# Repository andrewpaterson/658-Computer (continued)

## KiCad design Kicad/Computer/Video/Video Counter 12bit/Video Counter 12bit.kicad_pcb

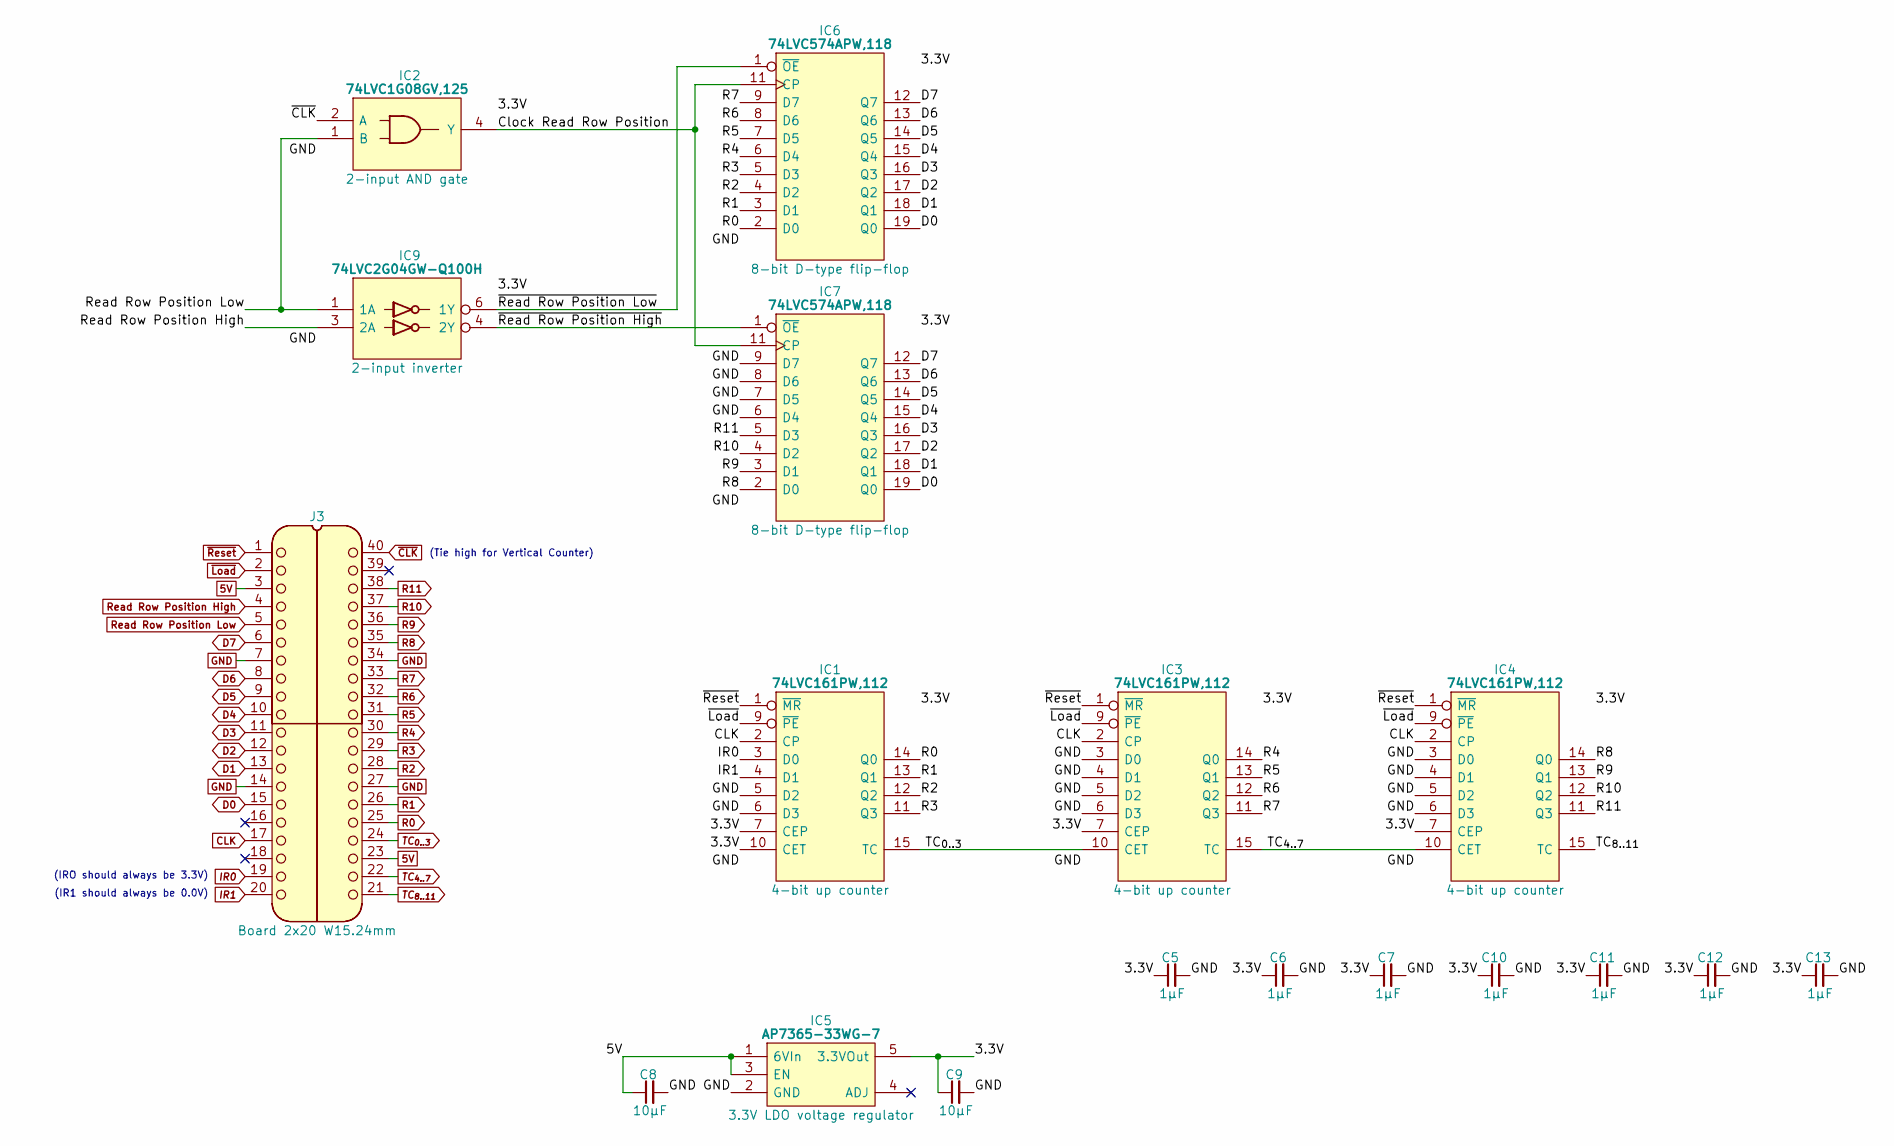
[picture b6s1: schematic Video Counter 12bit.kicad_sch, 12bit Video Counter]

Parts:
C5, C6, C7, C10, C11, C12, C13: 1μF; C_0805
C8, C9: 10µF; C_0805
IC1, IC3, IC4: 74LVC161PW,112; SOP65P640X110-16N; Mouser Part Number 771-LVC161PW112
IC2: 74LVC1G08GV,125; SOT95P275X110-5N; Manufacturer_Part_Number 74LVC1G08GV,125; Mouser Part Number 771-74LVC1G08GV
IC5: AP7365-33WG-7; SOT95P285X130-5N; Manufacturer_Part_Number AP7365-33WG-7; Mouser Part Number 621-AP7365-33WG-7
IC6, IC7: 74LVC574APW,118; SOP65P640X110-20N; Manufacturer_Part_Number 74LVC574APW,118; Mouser Part Number 771-74LVC574APW-T
IC9: 74LVC2G04GW-Q100H; SOP65P210X110-6N; Manufacturer_Part_Number 74LVC2G04GW-Q100H; Mouser Part Number 771-74LVC2G04GWQ100H
J3: Board 2x20 W15.24mm; DIP-40_Board_W15.24mm

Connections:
5V: C8.1, IC5.1 (6VIn), IC5.3 (EN), J3.3, J3.23
/3.3V: C5.1, C6.1, C7.1, C9.1, C10.1, C11.1, C12.1, C13.1, IC1.7 (CEP), IC1.10 (CET), IC1.16 (3V), IC2.5 (3V), IC3.7 (CEP), IC3.16 (3V), IC4.7 (CEP), IC4.16 (3V), IC5.5 (3.3VOut), IC6.20 (3V), IC7.20 (3V), IC9.5 (3V)
/Clock Read Row Position: IC2.4 (Y), IC6.11 (CP), IC7.11 (CP)
/~Read Row Position High: IC7.1 (~OE), IC9.4 (2Y)
/~Read Row Position Low: IC6.1 (~OE), IC9.6 (1Y)
CLK: IC1.2 (CP), IC3.2 (CP), IC4.2 (CP), J3.17
D0: IC6.19 (Q0), IC7.19 (Q0), J3.15
D1: IC6.18 (Q1), IC7.18 (Q1), J3.13
D2: IC6.17 (Q2), IC7.17 (Q2), J3.12
D3: IC6.16 (Q3), IC7.16 (Q3), J3.11
D4: IC6.15 (Q4), IC7.15 (Q4), J3.10
D5: IC6.14 (Q5), IC7.14 (Q5), J3.9
D6: IC6.13 (Q6), IC7.13 (Q6), J3.8
D7: IC6.12 (Q7), IC7.12 (Q7), J3.6
GND: C5.2, C6.2, C7.2, C8.2, C9.2, C10.2, C11.2, C12.2, C13.2, IC1.5 (D2), IC1.6 (D3), IC1.8 (GND), IC2.3 (GND), IC3.3 (D0), IC3.4 (D1), IC3.5 (D2), IC3.6 (D3), IC3.8 (GND), IC4.3 (D0), IC4.4 (D1), IC4.5 (D2), IC4.6 (D3), IC4.8 (GND), IC5.2 (GND), IC6.10 (GND), IC7.6 (D4), IC7.7 (D5), IC7.8 (D6), IC7.9 (D7), IC7.10 (GND), IC9.2 (GND), J3.7, J3.14, J3.27, J3.34
IR0: IC1.3 (D0), J3.19
IR1: IC1.4 (D1), J3.20
R0: IC1.14 (Q0), IC6.2 (D0), J3.25
R1: IC1.13 (Q1), IC6.3 (D1), J3.26
R2: IC1.12 (Q2), IC6.4 (D2), J3.28
R3: IC1.11 (Q3), IC6.5 (D3), J3.29
R4: IC3.14 (Q0), IC6.6 (D4), J3.30
R5: IC3.13 (Q1), IC6.7 (D5), J3.31
R6: IC3.12 (Q2), IC6.8 (D6), J3.32
R7: IC3.11 (Q3), IC6.9 (D7), J3.33
R8: IC4.14 (Q0), IC7.2 (D0), J3.35
R9: IC4.13 (Q1), IC7.3 (D1), J3.36
R10: IC4.12 (Q2), IC7.4 (D2), J3.37
R11: IC4.11 (Q3), IC7.5 (D3), J3.38
Read Row Position High: IC9.3 (2A), J3.4
Read Row Position Low: IC2.1 (B), IC9.1 (1A), J3.5
TC_{0..3}: IC1.15 (TC), IC3.10 (CET), J3.24
TC_{4..7}: IC3.15 (TC), IC4.10 (CET), J3.22
TC_{8..11}: IC4.15 (TC), J3.21
~CLK: IC2.2 (A), J3.40
~Load: IC1.9 (~PE), IC3.9 (~PE), IC4.9 (~PE), J3.2
~Reset: IC1.1 (~MR), IC3.1 (~MR), IC4.1 (~MR), J3.1

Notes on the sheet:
(Tie high for Vertical Counter)
(IRO should always be 3.3V)
(IR1 should always be 0.0V)

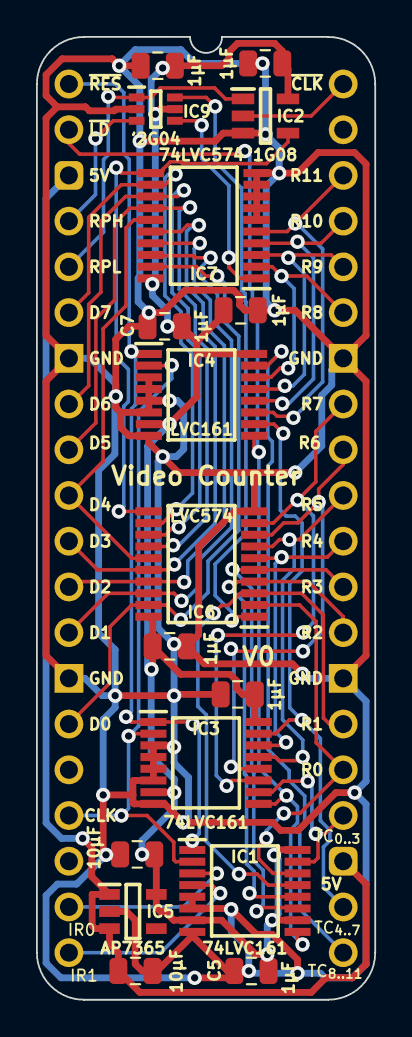
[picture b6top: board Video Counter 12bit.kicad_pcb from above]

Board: 2 copper layers, 18.8 x 53.5 mm, 18 parts (0 on the bottom side), 37 nets.

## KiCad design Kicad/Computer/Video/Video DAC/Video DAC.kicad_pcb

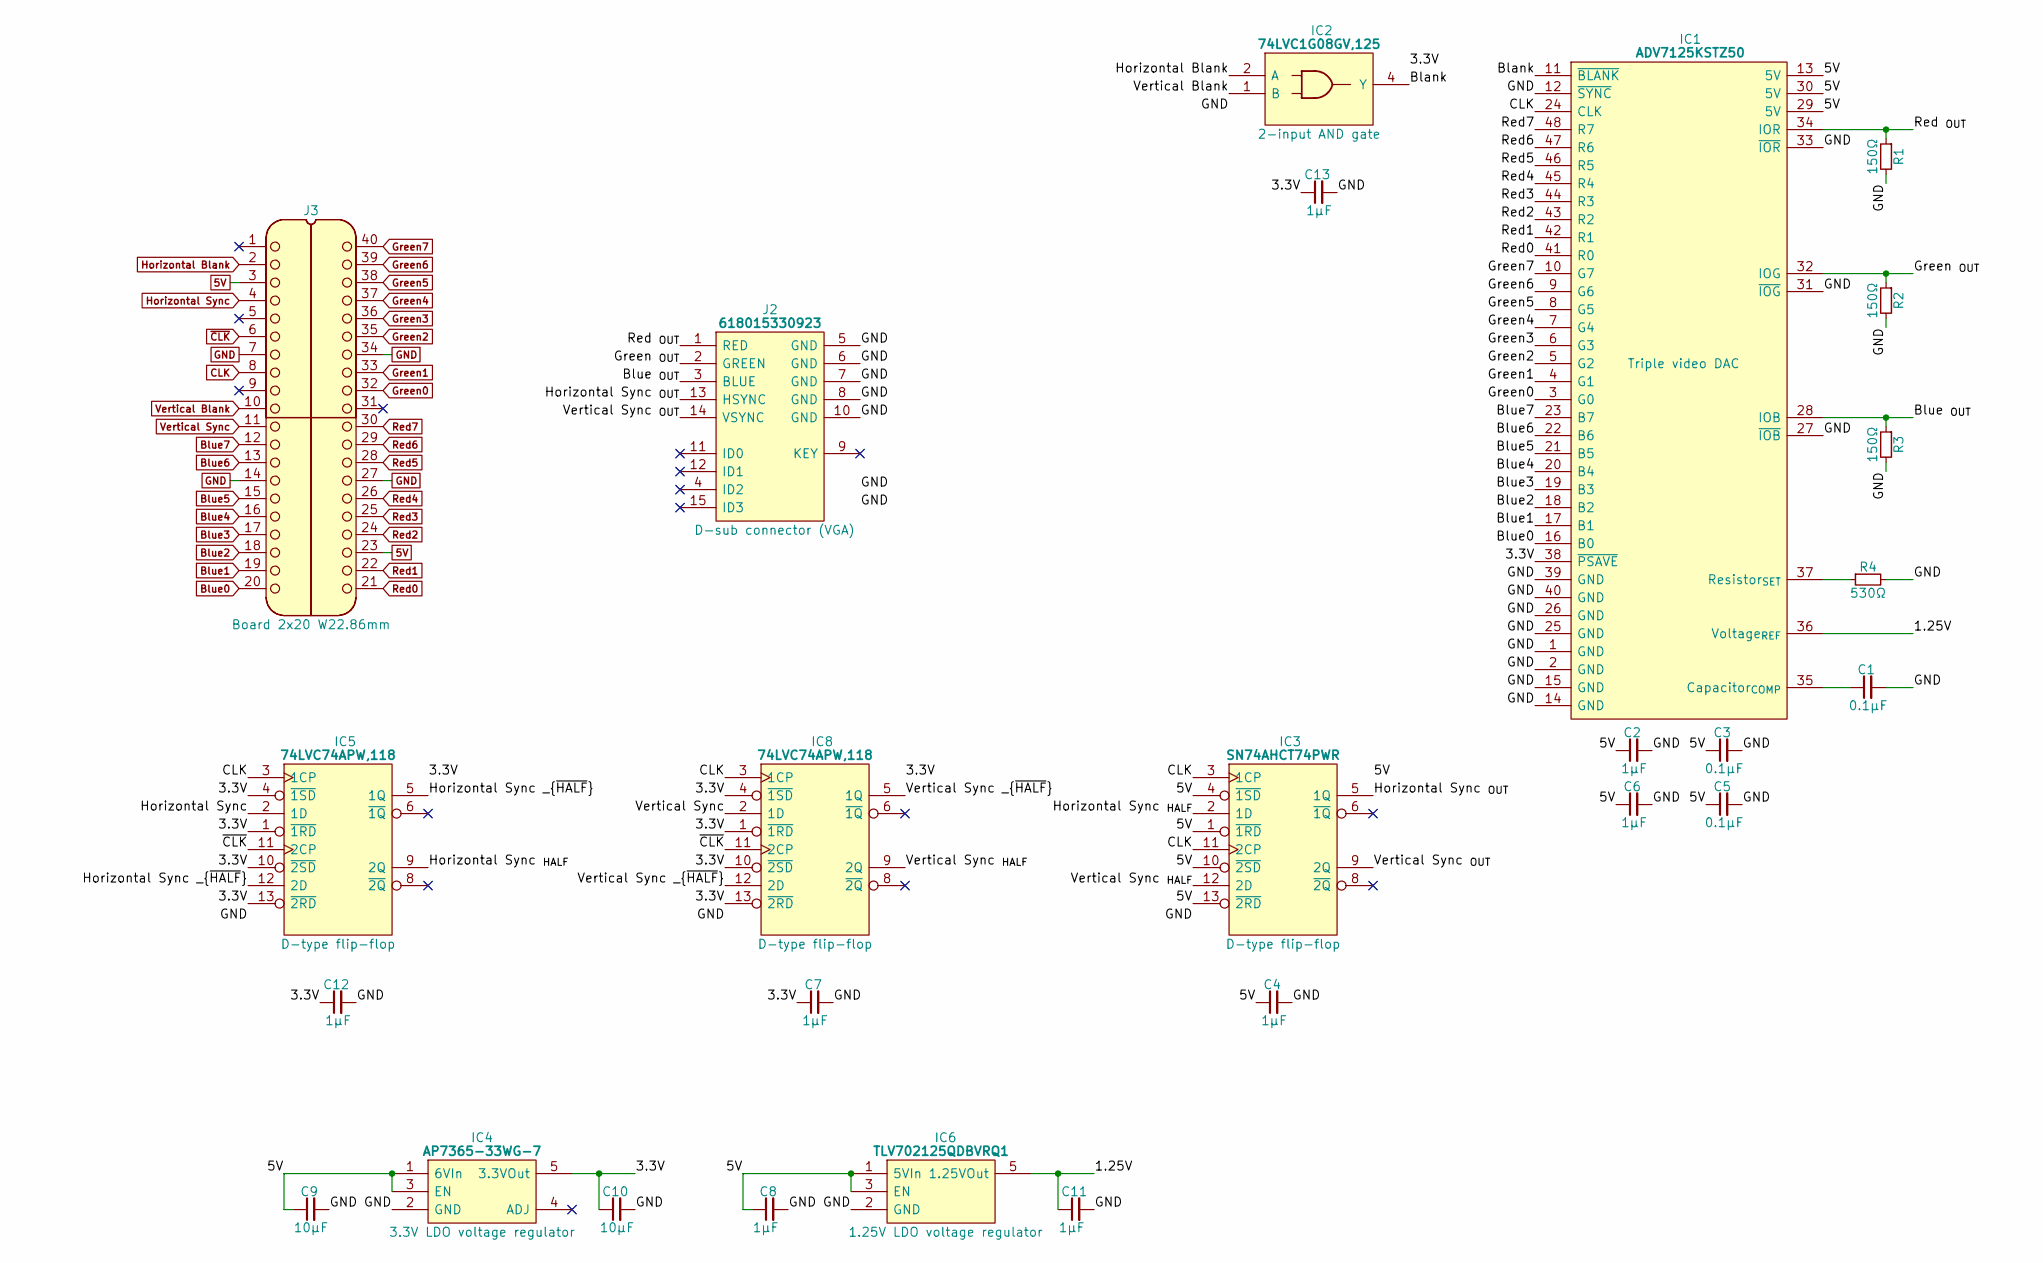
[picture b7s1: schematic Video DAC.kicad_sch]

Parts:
C1, C3, C5: 0.1μF; C_0805
C2, C4, C6, C7, C12, C13: 1μF; C_0805
C8, C11: 1µF; C_0805
C9, C10: 10µF; C_0805
IC1: ADV7125KSTZ50; QFP50P900X900X160-48N; Mouser Part Number 584-ADV7125KSTZ50
IC2: 74LVC1G08GV,125; SOT95P275X110-5N; Manufacturer_Part_Number 74LVC1G08GV,125; Mouser Part Number 771-74LVC1G08GV
IC3: SN74AHCT74PWR; SOP65P640X110-14N; Mouser Part Number 595-SN74AHCT74PWR
IC4: AP7365-33WG-7; SOT95P285X130-5N; Manufacturer_Part_Number AP7365-33WG-7; Mouser Part Number 621-AP7365-33WG-7
IC5, IC8: 74LVC74APW,118; SOP65P640X110-14N; Mouser Part Number 771-74LVC74APW-T
IC6: TLV702125QDBVRQ1; SOT95P280X145-5N; Manufacturer_Part_Number TLV702125QDBVRQ1; Mouser Part Number 595-TLV702125QDBVRQ1
J2: 618015330923; Manufacturer_Part_Number 618015330923; Mouser Part Number 710-618015330923
J3: Board 2x20 W22.86mm; DIP-40_Board_W22.86mm_Nak
R1, R2, R3: 150Ω; R_0805
R4: 530Ω; R_0805

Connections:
5V: C2.1, C3.1, C4.1, C5.1, C6.1, C8.1, C9.1, IC1.13 (5V), IC1.29 (5V), IC1.30 (5V), IC3.1 (~1RD), IC3.4 (~1SD), IC3.10 (~2SD), IC3.13 (~2RD), IC3.14 (5V), IC4.1 (6VIn), IC4.3 (EN), IC6.1 (5VIn), IC6.3 (EN), J3.3, J3.23
/1.25V: C11.1, IC1.36 (Voltage_{REF}), IC6.5 (1.25VOut)
/3.3V: C7.1, C10.1, C12.1, C13.1, IC1.38 (~PSAVE), IC2.5 (3V), IC4.5 (3.3VOut), IC5.1 (~1RD), IC5.4 (~1SD), IC5.10 (~2SD), IC5.13 (~2RD), IC5.14 (3V), IC8.1 (~1RD), IC8.4 (~1SD), IC8.10 (~2SD), IC8.13 (~2RD), IC8.14 (3V)
/Blank: IC1.11 (~BLANK), IC2.4 (Y)
/Blue _{OUT}: IC1.28 (IOB), J2.3 (BLUE), R3.1
/Green _{OUT}: IC1.32 (IOG), J2.2 (GREEN), R2.1
/Horizontal Sync _{HALF}: IC3.2 (1D), IC5.9 (2Q)
/Horizontal Sync _{OUT}: IC3.5 (1Q), J2.13 (HSYNC)
/Horizontal Sync _{~HALF}: IC5.5 (1Q), IC5.12 (2D)
/Red _{OUT}: IC1.34 (IOR), J2.1 (RED), R1.1
/Vertical Sync _{HALF}: IC3.12 (2D), IC8.9 (2Q)
/Vertical Sync _{OUT}: IC3.9 (2Q), J2.14 (VSYNC)
/Vertical Sync _{~HALF}: IC8.5 (1Q), IC8.12 (2D)
Blue0: IC1.16 (B0), J3.20
Blue1: IC1.17 (B1), J3.19
Blue2: IC1.18 (B2), J3.18
Blue3: IC1.19 (B3), J3.17
Blue4: IC1.20 (B4), J3.16
Blue5: IC1.21 (B5), J3.15
Blue6: IC1.22 (B6), J3.13
Blue7: IC1.23 (B7), J3.12
CLK: IC1.24 (CLK), IC3.3 (1CP), IC3.11 (2CP), IC5.3 (1CP), IC8.3 (1CP), J3.8
GND: C1.2, C2.2, C3.2, C4.2, C5.2, C6.2, C7.2, C8.2, C9.2, C10.2, C11.2, C12.2, C13.2, IC1.1 (GND), IC1.2 (GND), IC1.12 (~SYNC), IC1.14 (GND), IC1.15 (GND), IC1.25 (GND), IC1.26 (GND), IC1.27 (~IOB), IC1.31 (~IOG), IC1.33 (~IOR), IC1.39 (GND), IC1.40 (GND), IC2.3 (GND), IC3.7 (GND), IC4.2 (GND), IC5.7 (GND), IC6.2 (GND), IC8.7 (GND), J2.5 (GND), J2.6 (GND), J2.7 (GND), J2.8 (GND), J2.10 (GND), J2.MH1, J2.MH2, J3.7, J3.14, J3.27, J3.34, R1.2, R2.2, R3.2, R4.2
Green0: IC1.3 (G0), J3.32
Green1: IC1.4 (G1), J3.33
Green2: IC1.5 (G2), J3.35
Green3: IC1.6 (G3), J3.36
Green4: IC1.7 (G4), J3.37
Green5: IC1.8 (G5), J3.38
Green6: IC1.9 (G6), J3.39
Green7: IC1.10 (G7), J3.40
Horizontal Blank: IC2.2 (A), J3.2
Horizontal Sync: IC5.2 (1D), J3.4
unnamed: C1.1, IC1.35 (Capacitor_{COMP})
unnamed: IC1.37 (Resistor_{SET}), R4.1
Red0: IC1.41 (R0), J3.21
Red1: IC1.42 (R1), J3.22
Red2: IC1.43 (R2), J3.24
Red3: IC1.44 (R3), J3.25
Red4: IC1.45 (R4), J3.26
Red5: IC1.46 (R5), J3.28
Red6: IC1.47 (R6), J3.29
Red7: IC1.48 (R7), J3.30
Vertical Blank: IC2.1 (B), J3.10
Vertical Sync: IC8.2 (1D), J3.11
~CLK: IC5.11 (2CP), IC8.11 (2CP), J3.6

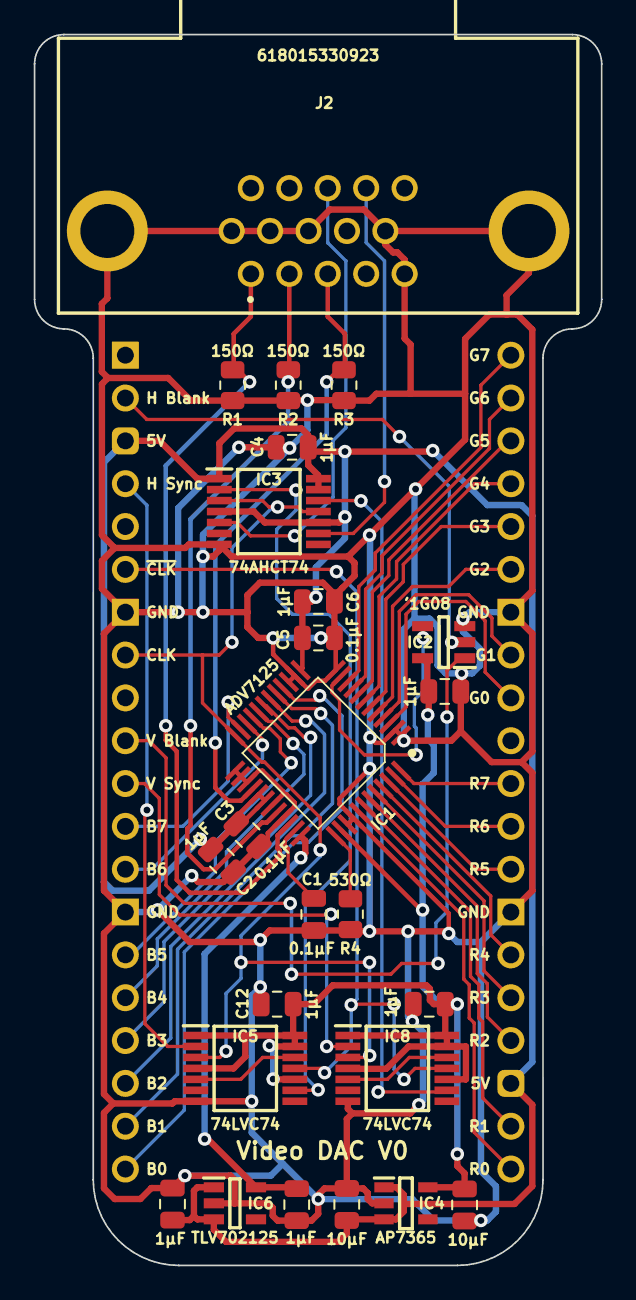
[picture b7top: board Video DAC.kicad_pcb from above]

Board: 2 copper layers, 33.6 x 73.0 mm, 26 parts (0 on the bottom side), 46 nets.
